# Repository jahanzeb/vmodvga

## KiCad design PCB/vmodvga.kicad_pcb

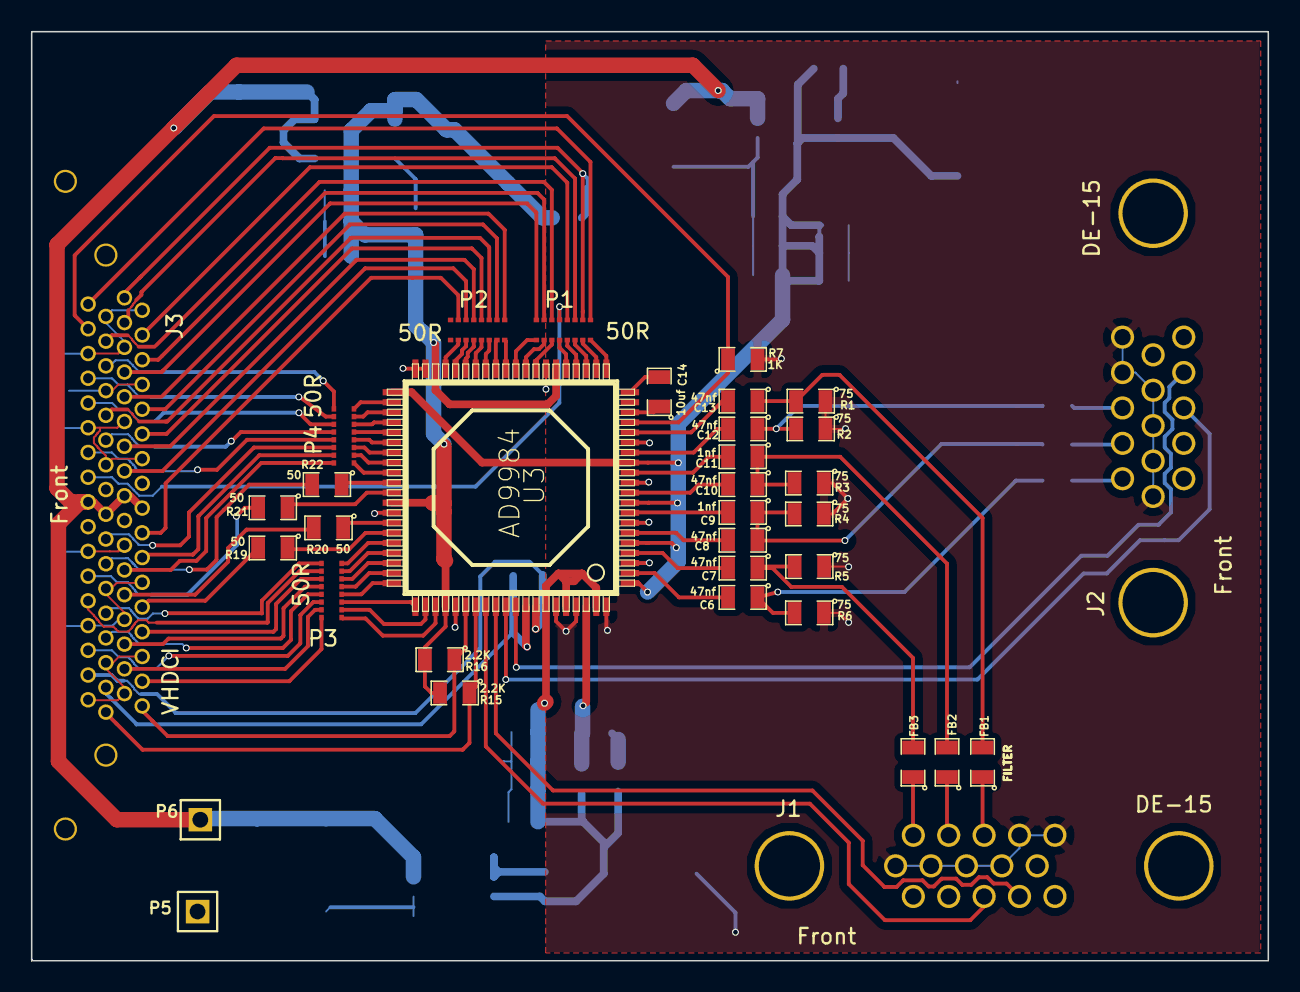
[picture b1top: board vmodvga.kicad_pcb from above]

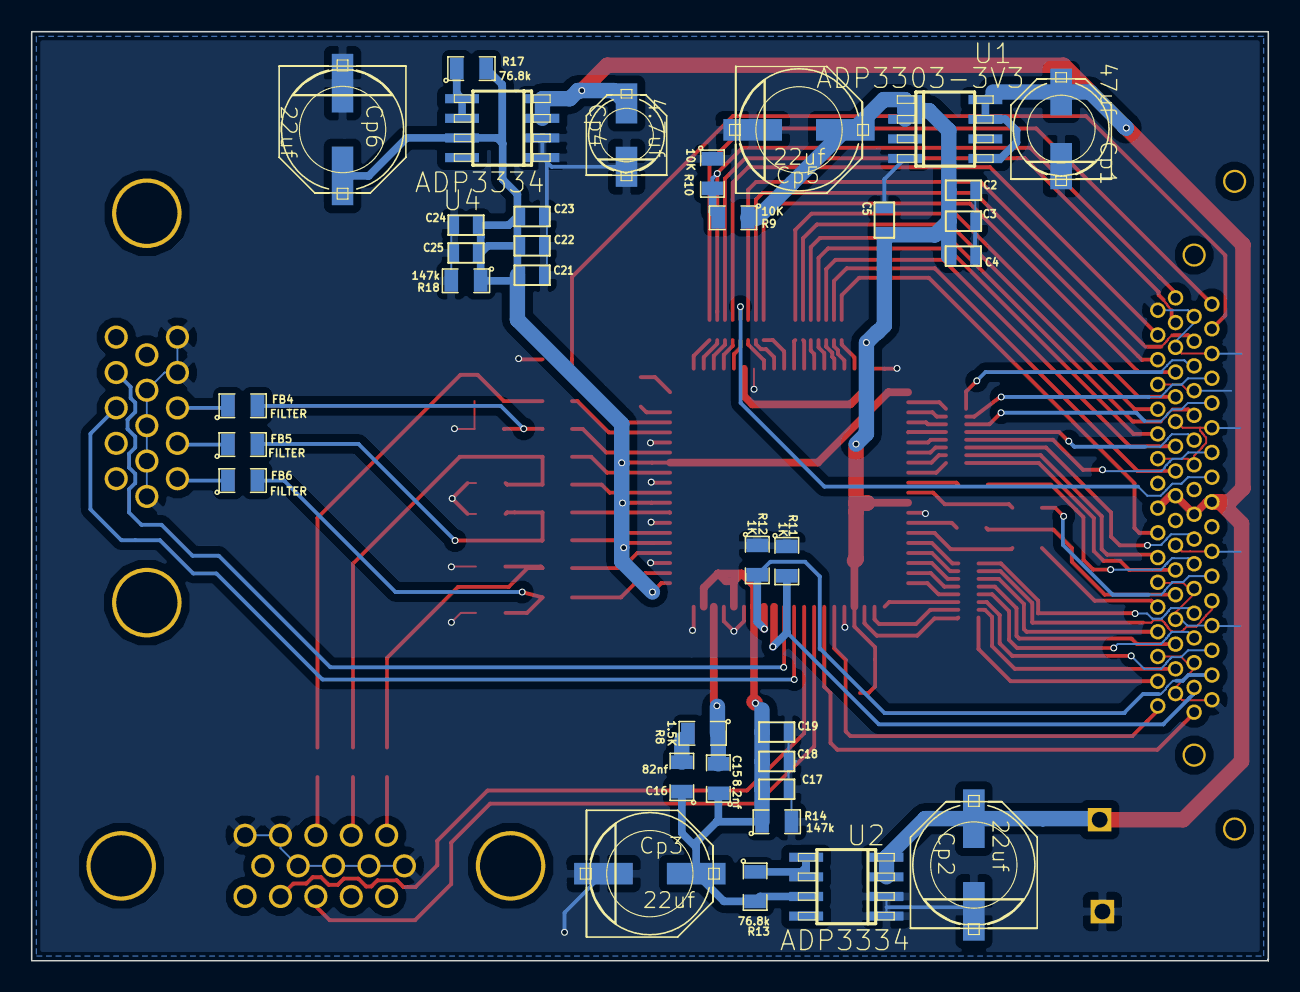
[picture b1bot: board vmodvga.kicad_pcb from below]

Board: 2 copper layers, 80.0 x 60.1 mm, 70 parts (35 on the bottom side), 110 nets.

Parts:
C2, C3, C4, C5, C17, C18, C19, C21, C22, C23, C24, C25: .1uf; SM0603
C6, C7, C8, C10, C12, C13: 47nf; SM0805
C9, C11: 1nf; SM0805
C14: 10uf; SM0805
C15: 8.2nf; SM0805
C16: 82nf; SM0805
Cp1: 47uf; -PANASONIC_D
Cp2, Cp3, Cp5, Cp6: 22uf; -PANASONIC_E
Cp4: 4.7uf; -PANASONIC_C
FB1, FB2, FB3, FB4, FB5, FB6: FILTER; SM0805
J1, J2: DE-15
J3: VHDCI
P1, P2, P3, P4: 50R; R50x8
P5, P6: CONN_1; PIN_ARRAY_1
R1, R2, R3, R4, R5, R6: 75; SM0805
R7, R11, R12: 1K; SM0805
R8: 1.5K; SM0805
R9, R10: 10K; SM0805
R13, R17: 76.8k; SM0805
R14, R18: 147k; SM0805
R15, R16: 2.2K; SM0805
R19, R20, R21, R22: 50; SM0805
U1: ADP3303-3V3; -SOIC8
U2, U4: ADP3334; -SOIC8
U3: AD9984; analog-devices2-LQFP80

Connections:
/B0: J3.32, P3.8
/B1: J3.31, P3.7
/B2: J3.63, P3.6
/B3: J3.62, P3.5
/B4: J3.29, P3.4
/B5: J3.28, P3.3
/B6: J3.59, P3.2
/B7: J3.60, P3.1
/B8: J3.26, R19.2
/B9: J3.25, R20.2
/CLAMP: J3.65, R12.2, U3.73
/COST: J3.66, R11.2, U3.72
/DATACK: J3.49, P1.13
/G0: J3.57, R21.2
/G1: J3.56, R22.2
/G2: J3.23, P4.16
/G3: J3.22, P4.15
/G4: J3.54, P4.14
/G5: J3.47, P4.13
/G6: J3.46, P4.12
/G7: J3.43, P4.11
/G8: J3.41, P4.10
/G9: J3.40, P4.9
/GND: C2.2, C3.2, C4.2, C5.2, C17.2, C18.2, C19.2, C21.2, C22.2, C23.2, C24.2, C25.2, Cp1.-, Cp2.-, Cp3.-, Cp4.-, Cp5.-, Cp6.-, J1.4, J1.5, J1.6, J1.7, J1.8, J1.9, J2.4, J2.5, J2.6, J2.7, J2.8, J2.9, J3.2, J3.5, J3.8, J3.11, J3.14, J3.21, J3.24, J3.27, J3.30, J3.33, J3.36, J3.39, J3.42, J3.45, J3.48, J3.55, J3.58, J3.61, J3.64, J3.67, P5.1, R1.1, R2.1, R3.1, R4.1, R5.1, R6.1, R7.2, R10.1, R11.1, R12.1, R14.2, R18.2, U1.4, U2.1, U2.2, U3.3, U3.7, U3.11, U3.15, U3.27, U3.39, U3.40, U3.53, U3.65, U3.75, U3.77, U3.80, U4.1, U4.2
/HSOUT: J3.3, P1.11
/HSYNC0: J2.13, U3.70
/HSYNC1: J1.13, U3.68
/OE_Field: J3.35, P1.9
/OVDD: C2.1, C3.1, C4.1, C5.1, Cp5.+, R9.1, R15.2, R16.2, U1.1, U1.2, U3.26, U3.38, U3.52, U3.64
/PVD: C15.1, C16.1, C17.1, C18.1, C19.1, Cp3.+, R13.2, R14.1, U2.7, U3.74, U3.76, U3.79
/PWRDWN: J3.37, R7.1, U3.17
/R0: J3.20, P2.15
/R1: J3.15, P2.14
/R2: J3.13, P2.13
/R3: J3.12, P2.12
/R4: J3.44, P2.11
/R5: J3.10, P2.10
/R6: J3.9, P2.9
/R7: J3.7, P1.16
/R8: J3.6, P1.15
/R9: J3.38, P1.14
/SCL: J3.68, R15.1, U3.67
/SDA: J3.34, R16.1, U3.66
/SOGOUT: J3.4, P1.12
/VCC: Cp1.+, Cp2.+, Cp4.+, J3.17, J3.18, J3.51, J3.52, P6.1, U1.5, U1.7, U1.8, U2.3, U2.4, U4.3, U4.4
/VD: C21.1, C22.1, C23.1, C24.1, C25.1, Cp6.+, R17.2, R18.1, U3.1, U3.5, U3.9, U3.13, U3.41, U4.7
/VSOUT: J3.1, P1.10, R9.2, R10.2
/VSYNC0: J2.14, U3.71
/VSYNC1: J1.14, U3.69
unnamed: R13.1, U2.5, U2.6
unnamed: R17.1, U4.5, U4.6
unnamed: C12.2, U3.14
unnamed: C8.2, U3.6
unnamed: C6.2, U3.2
unnamed: C9.2, U3.8
unnamed: C14.2, U3.20
unnamed: C14.1, U3.18
unnamed: R22.1, U3.50
unnamed: P3.12, U3.60
unnamed: P3.13, U3.59
unnamed: P3.14, U3.58
unnamed: P3.15, U3.57
unnamed: P3.16, U3.56
unnamed: R19.1, U3.55
unnamed: R20.1, U3.54
unnamed: R21.1, U3.51
unnamed: P4.1, U3.49
unnamed: P4.2, U3.48
unnamed: P4.3, U3.47
unnamed: P4.4, U3.46
unnamed: P4.5, U3.45
unnamed: P4.6, U3.44
unnamed: P4.7, U3.43
unnamed: P4.8, U3.42
unnamed: P3.10, U3.62
unnamed: P1.2, U3.29
unnamed: P1.1, U3.30
unnamed: P2.8, U3.31
unnamed: P2.7, U3.32
unnamed: P2.6, U3.33
unnamed: P2.5, U3.34
unnamed: P2.4, U3.35
unnamed: P2.3, U3.36
unnamed: P2.2, U3.37
unnamed: P3.11, U3.61
unnamed: P1.3, U3.28
unnamed: P3.9, U3.63
unnamed: FB4.1, J2.3
unnamed: FB6.1, J2.1
unnamed: P1.8, U3.21
unnamed: P1.7, U3.22
unnamed: P1.6, U3.23
unnamed: P1.5, U3.24
unnamed: P1.4, U3.25
unnamed: C7.1, FB3.2, R5.2
unnamed: C13.1, FB1.2, R1.2
unnamed: C8.1, C9.1, FB5.2, R4.2
unnamed: C6.1, FB6.2, R6.2
unnamed: FB1.1, J1.3
unnamed: FB2.1, J1.2
unnamed: FB3.1, J1.1
unnamed: FB5.1, J2.2
unnamed: C12.1, FB4.2, R2.2
unnamed: C16.2, R8.2
unnamed: C10.1, C11.1, FB2.2, R3.2
unnamed: C10.2, U3.10
unnamed: C11.2, U3.12
unnamed: C13.2, U3.16
unnamed: C7.2, U3.4
unnamed: C15.2, R8.1, U3.78

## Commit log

2013-07-31 VHDCI Connector footprint verified and GND plane added to top layer.
2013-07-31 Ground plane modified
2013-07-31 GND plan changed
2013-07-31 Drill size added manually to txt file
2013-07-31 PDF files updated.
